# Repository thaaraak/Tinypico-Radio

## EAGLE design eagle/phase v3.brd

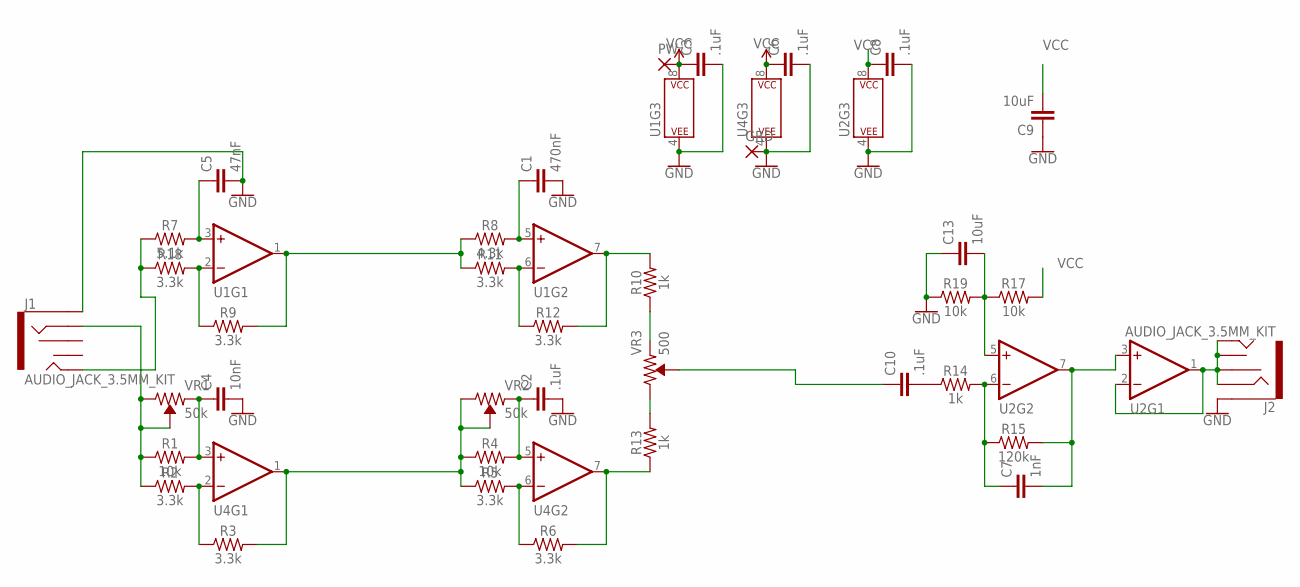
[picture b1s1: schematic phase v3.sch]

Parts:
C1: 470nF; 0805
C2, C3, C6, C8, C10: .1uF; 0805
C4: 10nF; 0805
C5: 47nF; 0805
C7: 1nF; 0805
C9, C13: 10uF; C5B3.5
GRD: 2,54/1,1
J1, J2: AUDIO_JACK_3.5MM_KIT; AUDIO-JACK-KIT
PW: 2,54/1,1
R1, R4, R17, R19: 10k; 0805
R2, R3, R5, R6, R9, R11, R12, R18: 3.3k; 0805
R7: 5.1k; 0805
R8: 4.3k; 0805
R10, R13, R14: 1k; 0805
R15: 120k; 0805
U1, U2, U4: LM358DIP08-SOIC; SO08
VR1, VR2: 50k; TRIMPOT-PTH-3386U
VR3: 500; TRIMPOT-PTH-3386U

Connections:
GND: C1.2, C2.2, C3.2, C4.2, C5.2, C6.2, C8.2, C9.1, C13.1, GRD.1, J1.SLEEVE, J2.SLEEVE, R19.1, U1.4 (P$V-), U2.4 (P$V-), U4.4 (P$V-)
unnamed: C4.1, R1.2, U4.3 (+IN), VR1.1 (CCW)
unnamed: R2.2, R3.1, U4.2 (-IN)
unnamed: R3.2, R4.1, R5.1, U4.1 (OUT), VR2.2 (WIPER), VR2.3 (CW)
unnamed: J1.RING, R1.1, R2.1, VR1.2 (WIPER), VR1.3 (CW)
unnamed: C2.1, R4.2, U4.5 (+IN), VR2.1 (CCW)
unnamed: R5.2, R6.1, U4.6 (-IN)
unnamed: R9.1, R18.2, U1.2 (-IN)
unnamed: R6.2, R13.1, U4.7 (OUT)
unnamed: C5.1, R7.2, U1.3 (+IN)
unnamed: J1.TIP, R7.1, R18.1
unnamed: C1.1, R8.2, U1.5 (+IN)
unnamed: R8.1, R9.2, R11.1, U1.1 (OUT)
unnamed: R11.2, R12.1, U1.6 (-IN)
unnamed: R10.1, VR3.1 (CCW)
unnamed: R10.2, R12.2, U1.7 (OUT)
unnamed: R13.2, VR3.3 (CW)
unnamed: C10.2, R14.1
unnamed: C10.1, VR3.2 (WIPER)
unnamed: C7.2, R15.2, U2.3 (+IN), U2.7 (OUT)
unnamed: C13.2, R17.1, R19.2, U2.5 (+IN)
unnamed: C7.1, R14.2, R15.1, U2.6 (-IN)
unnamed: J2.RING, J2.RSH, J2.TIP, J2.TSH, U2.1 (OUT), U2.2 (-IN)
VCC: C3.1, C6.1, C8.1, C9.2, PW.1, R17.2, U1.8 (P$V+), U2.8 (P$V+), U4.8 (P$V+)

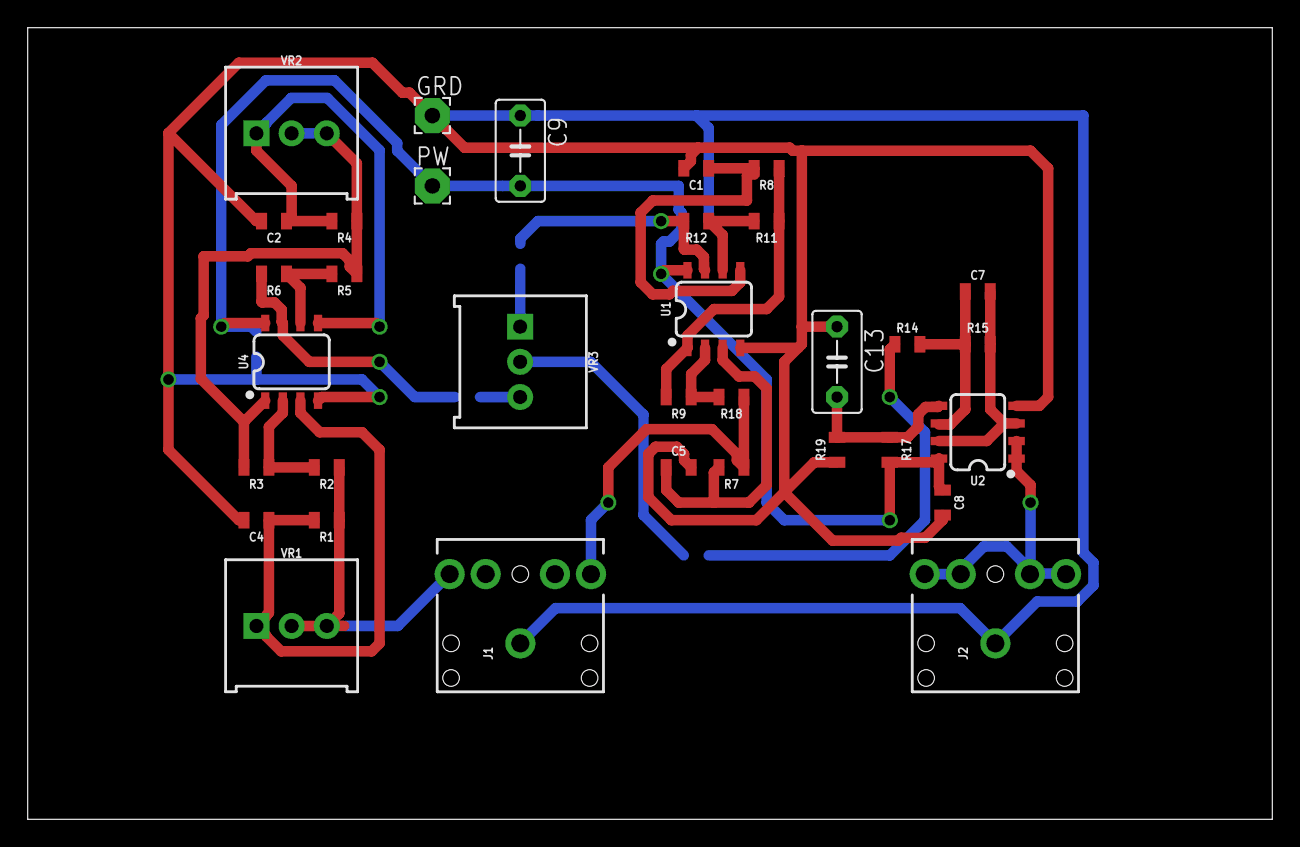
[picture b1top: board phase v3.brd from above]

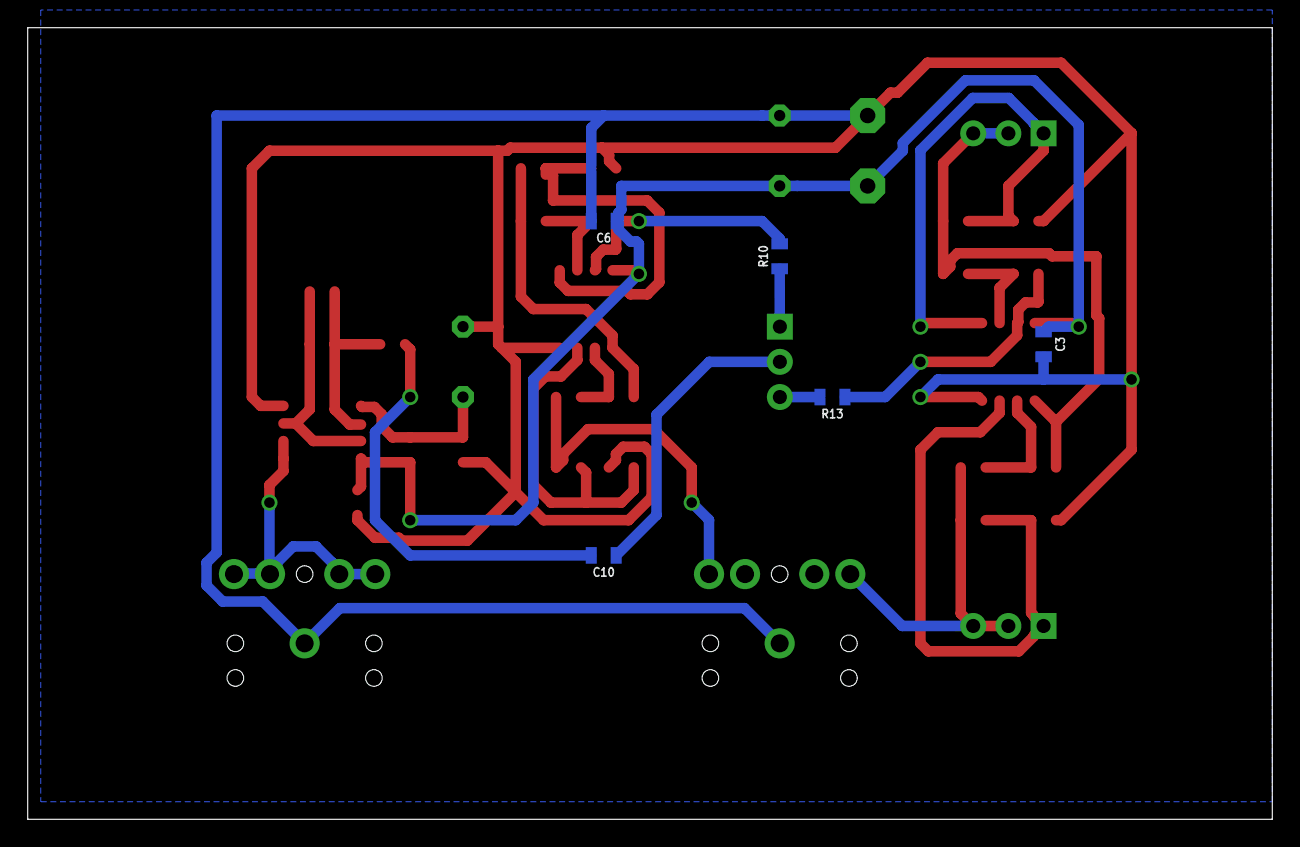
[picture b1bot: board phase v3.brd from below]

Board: 2 copper layers, 89.8 x 57.1 mm, 39 parts (5 on the bottom side), 24 nets.

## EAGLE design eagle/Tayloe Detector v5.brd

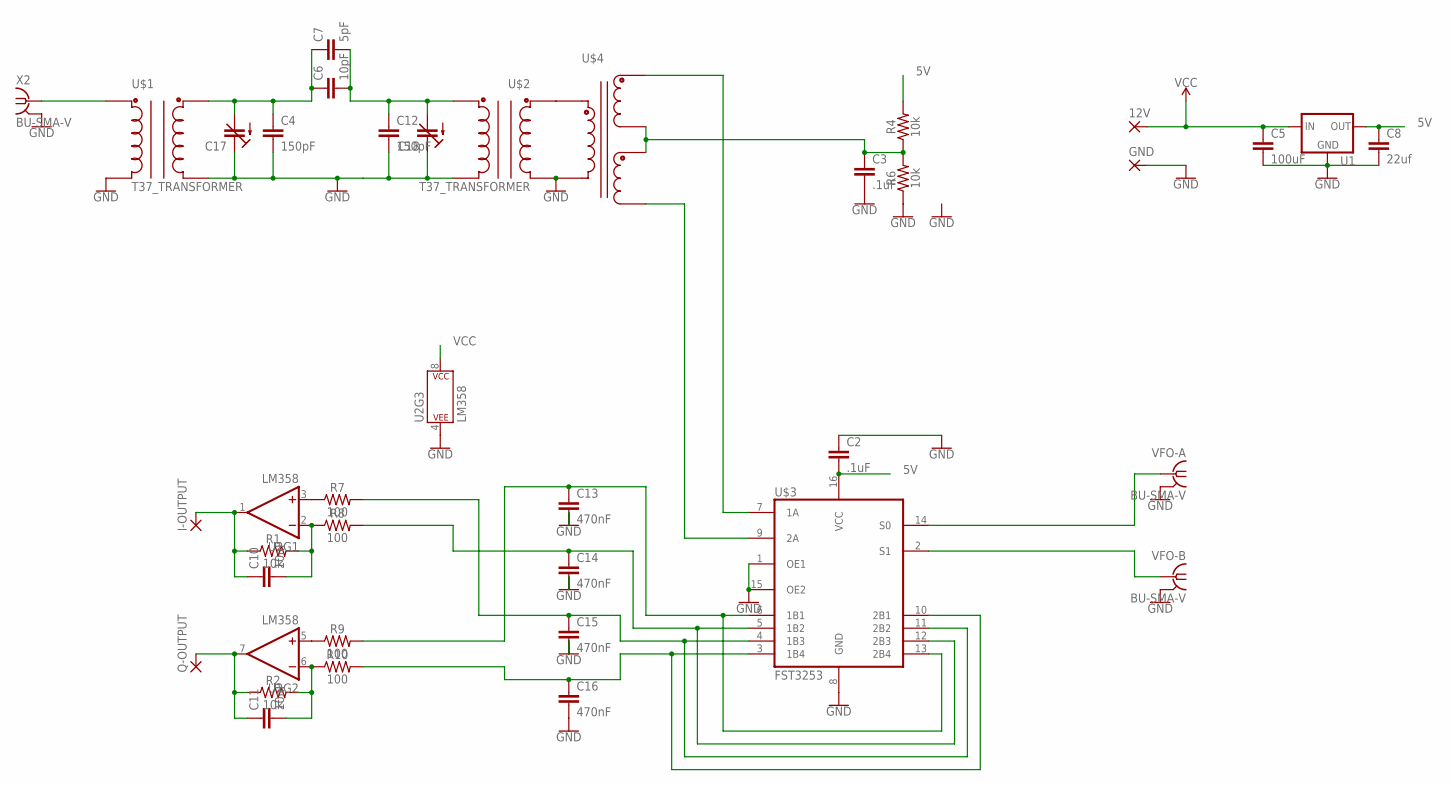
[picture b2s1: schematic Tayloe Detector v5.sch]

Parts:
12V: 3,17/1,1
C2, C3: .1uF; C5B3.5
C4, C12: 150pF; C5B3.5
C5: 100uF; C5B3.5
C6: 10pF; C5B3.5
C7: 5pF; C5B3.5
C8: 22uf; C5B3.5
C10, C11: 10nF; C5B3.5
C13, C14, C15, C16: 470nF; C5B3.5
C17, C18: C-TRIMMTZ03; CTRIMTZ03
GND: 3,17/1,1
I-OUTPUT: 3,17/1,1
Q-OUTPUT: 3,17/1,1
R1, R2, R4, R6: 10k; AXIAL-0.3
R7, R8, R9, R10: 100; AXIAL-0.3
U1: V_REG_78XXTO-92_UNTESTED; TO-92
U2: LM358; DIP08
U$1, U$2: T37_TRANSFORMER
U$3: FST3253; SO16
U$4: T50_SPLITTER
VFO-A: BU-SMA-V
VFO-B: BU-SMA-V
X2: BU-SMA-V

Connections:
5V: C2.2, C8.1, R4.P$2 (2), U1.1 (OUT), U$3.16 (VCC)
GND: C2.1, C3.2, C4.2, C5.2, C8.2, C12.2, C13.2, C14.2, C15.2, C16.2, C17.1 (E), C18.1 (E), GND.1, R6.P$1 (1), U1.2 (GND), U2.4 (P$V-), U$1.C1A, U$1.C2A, U$2.C1A, U$2.C2A, U$3.1 (OE1), U$3.8 (GND), U$3.15 (OE2), U$4.C1A, VFO-A.2, VFO-A.3 (2), VFO-A.4 (2), VFO-A.5 (2), VFO-B.2, VFO-B.3 (2), VFO-B.4 (2), VFO-B.5 (2), X2.2, X2.3 (2), X2.4 (2), X2.5 (2)
unnamed: C13.1, R9.P$2 (2), U$3.6 (1B1), U$3.13 (2B4)
unnamed: R7.P$1 (1), U2.3 (+IN)
unnamed: C16.1, R10.P$2 (2), U$3.3 (1B4), U$3.10 (2B1)
unnamed: C4.1, C6.1, C7.1, C17.2 (A), U$1.C2B
unnamed: C15.1, R7.P$2 (2), U$3.4 (1B3), U$3.11 (2B2)
unnamed: C10.2, R1.P$2 (2), R8.P$1 (1), U2.2 (-IN)
unnamed: C6.2, C7.2, C12.1, C18.2 (A), U$2.C2B
unnamed: R9.P$1 (1), U2.5 (+IN)
unnamed: U$1.C1B, X2.1
unnamed: C10.1, I-OUTPUT.1, R1.P$1 (1), U2.1 (OUT)
unnamed: C11.2, R2.P$2 (2), R10.P$1 (1), U2.6 (-IN)
unnamed: U$3.14 (S0), VFO-A.1
unnamed: C11.1, Q-OUTPUT.1, R2.P$1 (1), U2.7 (OUT)
unnamed: U$3.2 (S1), VFO-B.1
unnamed: U$3.7 (1A), U$4.C3B (C2B)
unnamed: C3.1, R4.P$1 (1), R6.P$2 (2), U$4.C2A (C3B), U$4.C3A (C2A)
unnamed: U$2.C1B, U$4.C1B
unnamed: C14.1, R8.P$2 (2), U$3.5 (1B2), U$3.12 (2B3)
unnamed: U$3.9 (2A), U$4.C2B (C3A)
VCC: 12V.1, C5.1, U1.3 (IN), U2.8 (P$V+)

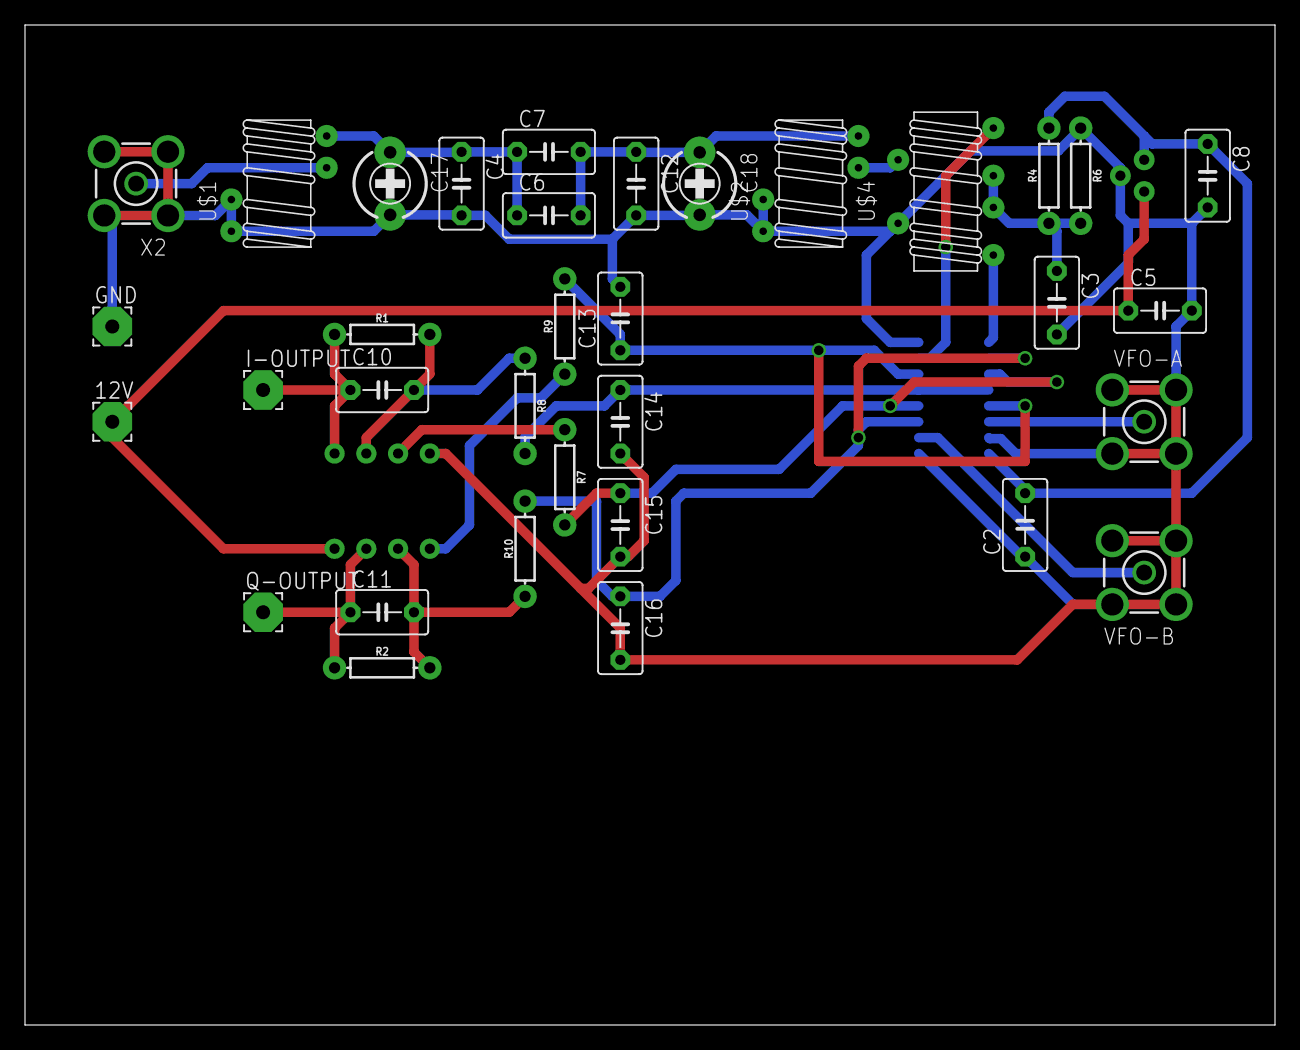
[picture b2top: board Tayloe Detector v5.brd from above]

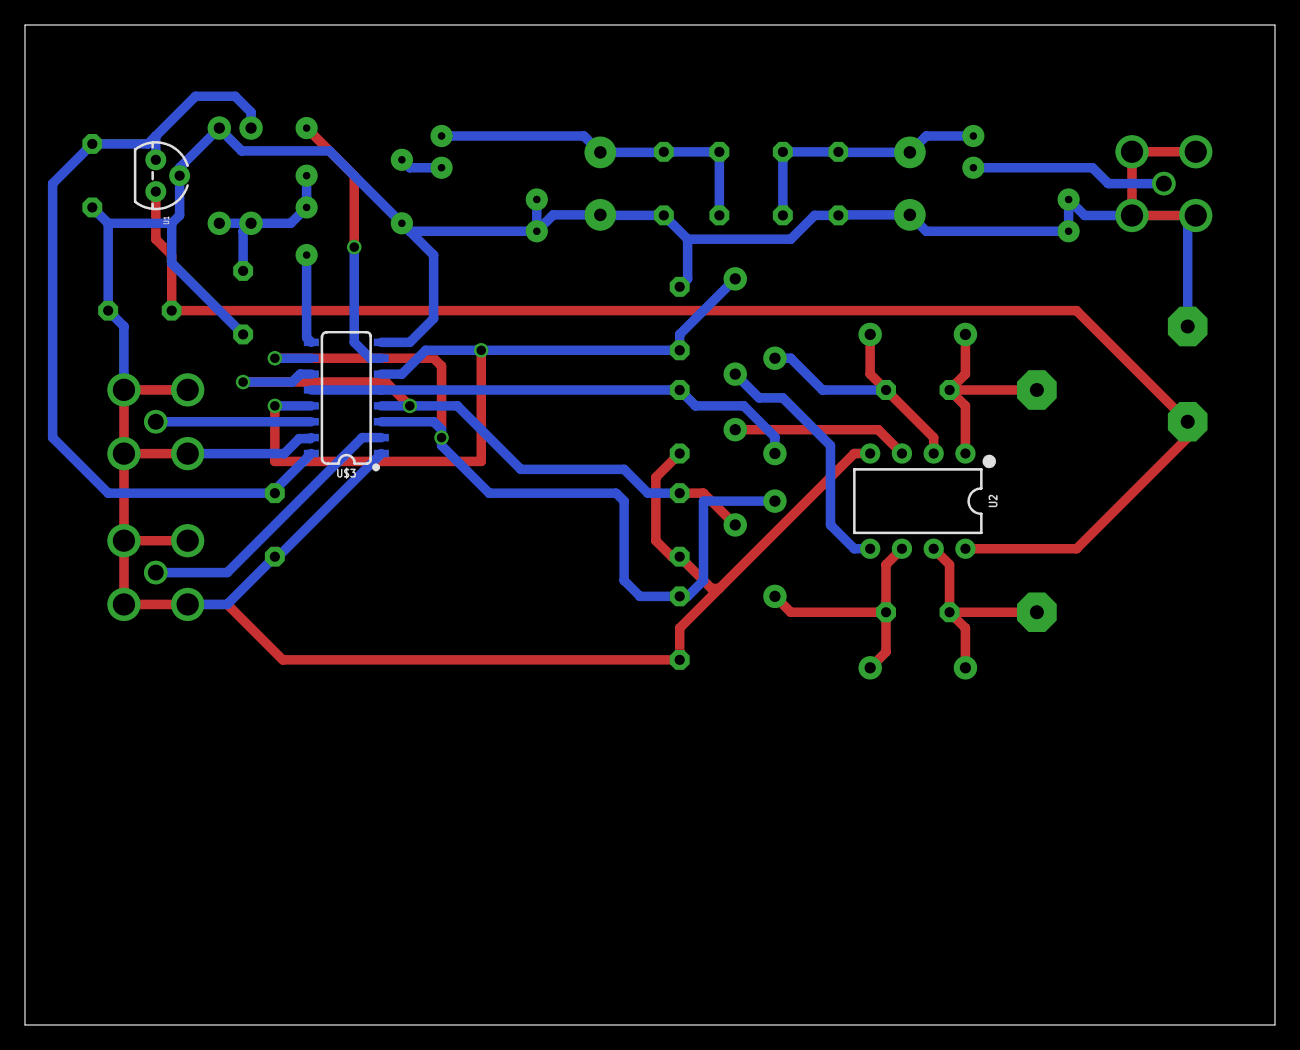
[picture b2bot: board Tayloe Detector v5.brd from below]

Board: 2 copper layers, 100.0 x 80.0 mm, 37 parts (3 on the bottom side), 22 nets.

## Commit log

2020-04-11 Copying from pi 4
2020-04-13 Added Tayloe
2020-04-14 Added ADS1115
2020-04-14 Commented out prints
2020-04-20 adding kicad
2020-04-27 Tinypico on board
2020-04-28 Trying to get rid of clicks
2020-04-29 Solved the clicks with Encoder
2020-05-01 Added Phase Shifter
2020-05-01 fix kicad
2020-05-06 fixing cap placement
2020-05-06 added bom
2020-05-06 added BOM and pdf schem,atic
2020-05-07 Added PDF for schematic
2020-05-09 added flter
2020-05-09 added board and schematic for receiver
2020-05-12 adding transmitter
2020-05-24 added PDFs
2020-05-25 replace T
2020-05-31 added mic amp

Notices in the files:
parts and their libraries:
SparkFun-IC-Power: Licensing: Creative Commons ShareAlike 4.0 International - https://creativecommons.org/licenses/by-sa/4.0
